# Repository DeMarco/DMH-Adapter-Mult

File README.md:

# DMH-Adapter-Mult
 Multiple module with 6.35mm, 3.5mm and Banana Jack adaptation

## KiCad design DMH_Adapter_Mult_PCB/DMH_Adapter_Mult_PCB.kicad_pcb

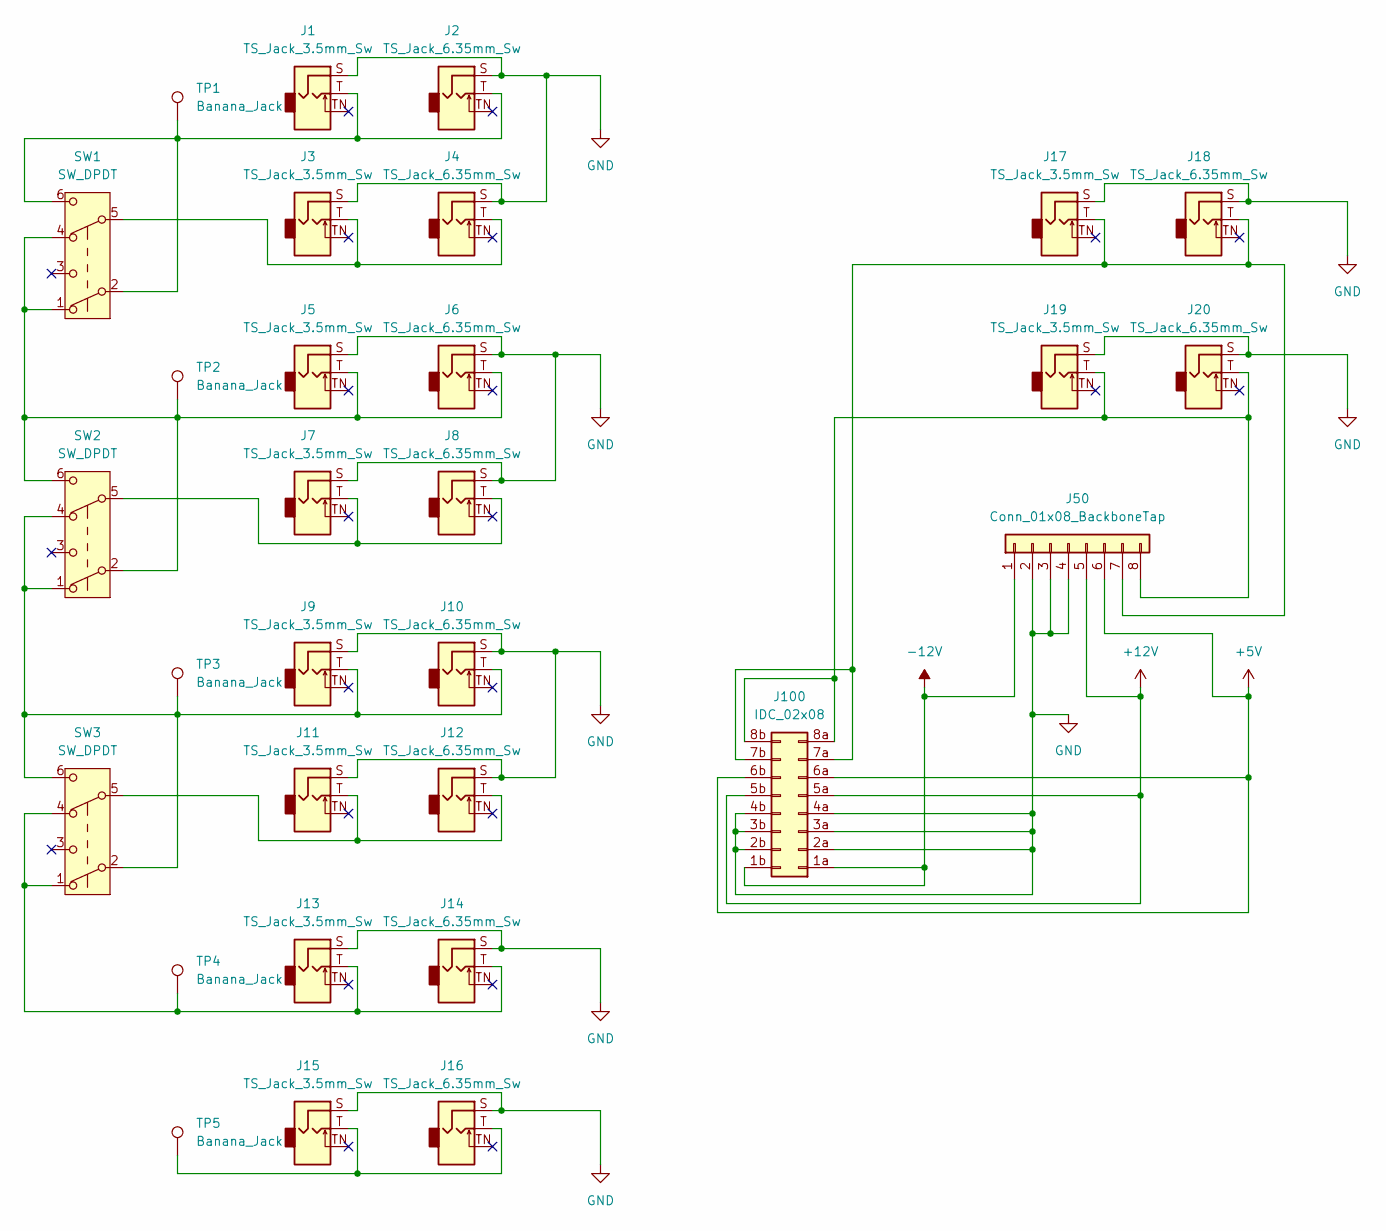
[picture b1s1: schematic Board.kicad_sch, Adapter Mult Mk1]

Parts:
J1, J3, J5, J7, J9, J11, J13, J15, J17, J19: TS_Jack_3.5mm_Sw; AMPHENOL_ACJM-MV35-2S
J2, J4, J6, J8, J10, J12, J14, J16, J18, J20: TS_Jack_6.35mm_Sw; CUI_MJ-63052A
J50: Conn_01x08_BackboneTap; PinHeader_1x08_P2.54mm_Vertical
J100: IDC_02x08; IDC-Header_2x08_P2.54mm_Vertical_Eurorack
SW1, SW2, SW3: SW_DPDT; PinHeader_2x03_P2.54mm_Vertical_142536
TP1, TP2, TP3, TP4, TP5: Banana_Jack; PinHeader_1x01_P2.54mm_Vertical

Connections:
+5V: J50.6, J100.6a, J100.6b
+12V: J50.5, J100.5a, J100.5b
-12V: J50.1, J100.1a, J100.1b
GND: J1.S, J2.S, J3.S, J4.S, J5.S, J6.S, J7.S, J8.S, J9.S, J10.S, J11.S, J12.S, J13.S, J14.S, J15.S, J16.S, J17.S, J18.S, J19.S, J20.S, J50.2, J50.3, J50.4, J100.2a, J100.2b, J100.3a, J100.3b, J100.4a, J100.4b
unnamed: J1.T, J2.T, SW1.2 (B), SW1.6 (C), TP1.1
unnamed: J3.T, J4.T, SW1.5 (B)
unnamed: J5.T, J6.T, SW1.1 (A), SW1.4 (A), SW2.2 (B), SW2.6 (C), TP2.1
unnamed: J7.T, J8.T, SW2.5 (B)
unnamed: J9.T, J10.T, SW2.1 (A), SW2.4 (A), SW3.2 (B), SW3.6 (C), TP3.1
unnamed: J11.T, J12.T, SW3.5 (B)
unnamed: J13.T, J14.T, SW3.1 (A), SW3.4 (A), TP4.1
unnamed: J15.T, J16.T, TP5.1
unnamed: J17.T, J18.T, J50.7, J100.7a, J100.7b
unnamed: J19.T, J20.T, J50.8, J100.8a, J100.8b

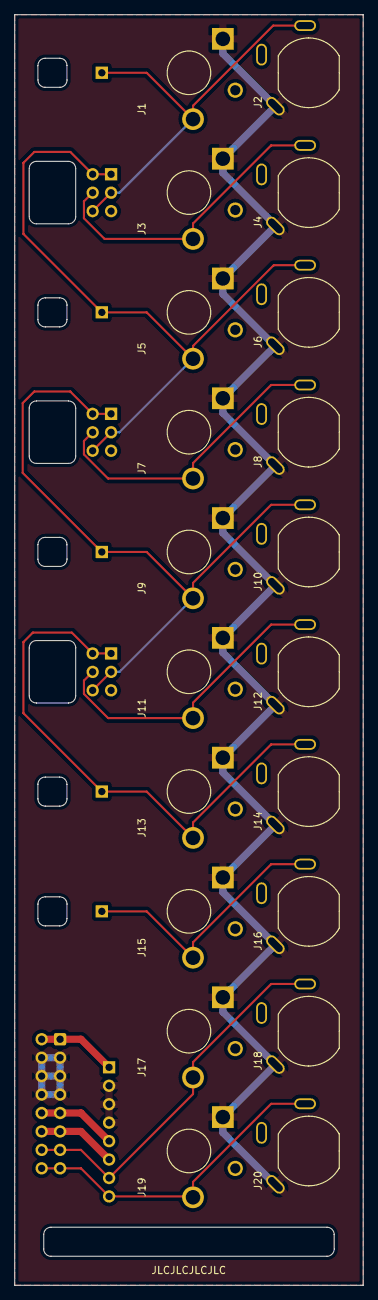
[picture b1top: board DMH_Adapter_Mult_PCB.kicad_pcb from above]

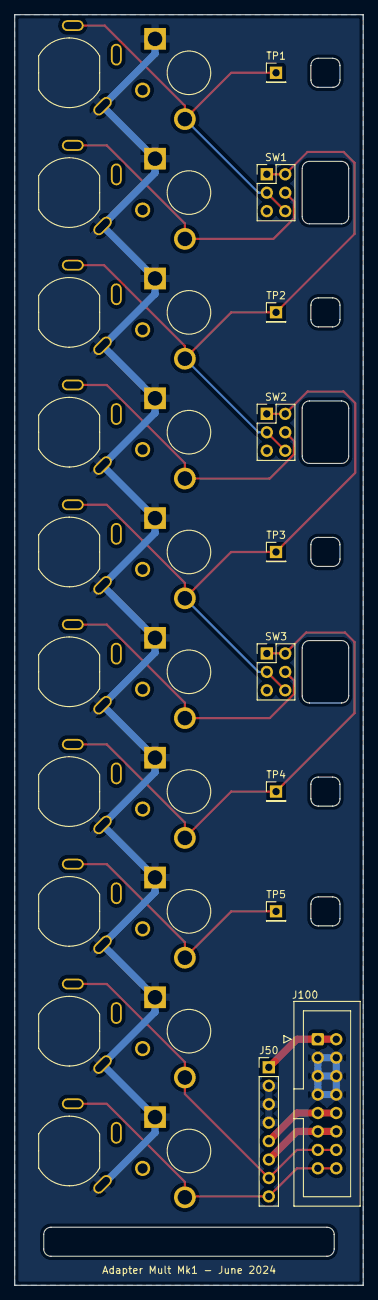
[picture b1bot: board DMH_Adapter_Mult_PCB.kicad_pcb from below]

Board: 2 copper layers, 48.0 x 175.0 mm, 30 parts (10 on the bottom side), 14 nets.

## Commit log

2024-06-27 Deleting untracked SynthStuff Libraries
2024-06-27 Re-added properly tracked SynthStuff Libraries
2024-06-27 Cache sync?
2024-06-28 Prepared Panel Gerbers
2024-06-29 Adjusted silkscreen text and constrains to JLCPCB capabilities
2024-06-29 Generated Gerbers
2024-06-29 Matched silkscreen text constraints to JLCPCB capa
2024-06-29 Sync libs
2024-06-29 Updated gitignore
2024-06-29 Regenerated panel Gerbers
2024-06-30 Unstaged unneeded files
2024-07-11 Synced SynthStuff library
2024-09-21 Copied board stackup configs from another board
2026-03-12 Kicad 9
